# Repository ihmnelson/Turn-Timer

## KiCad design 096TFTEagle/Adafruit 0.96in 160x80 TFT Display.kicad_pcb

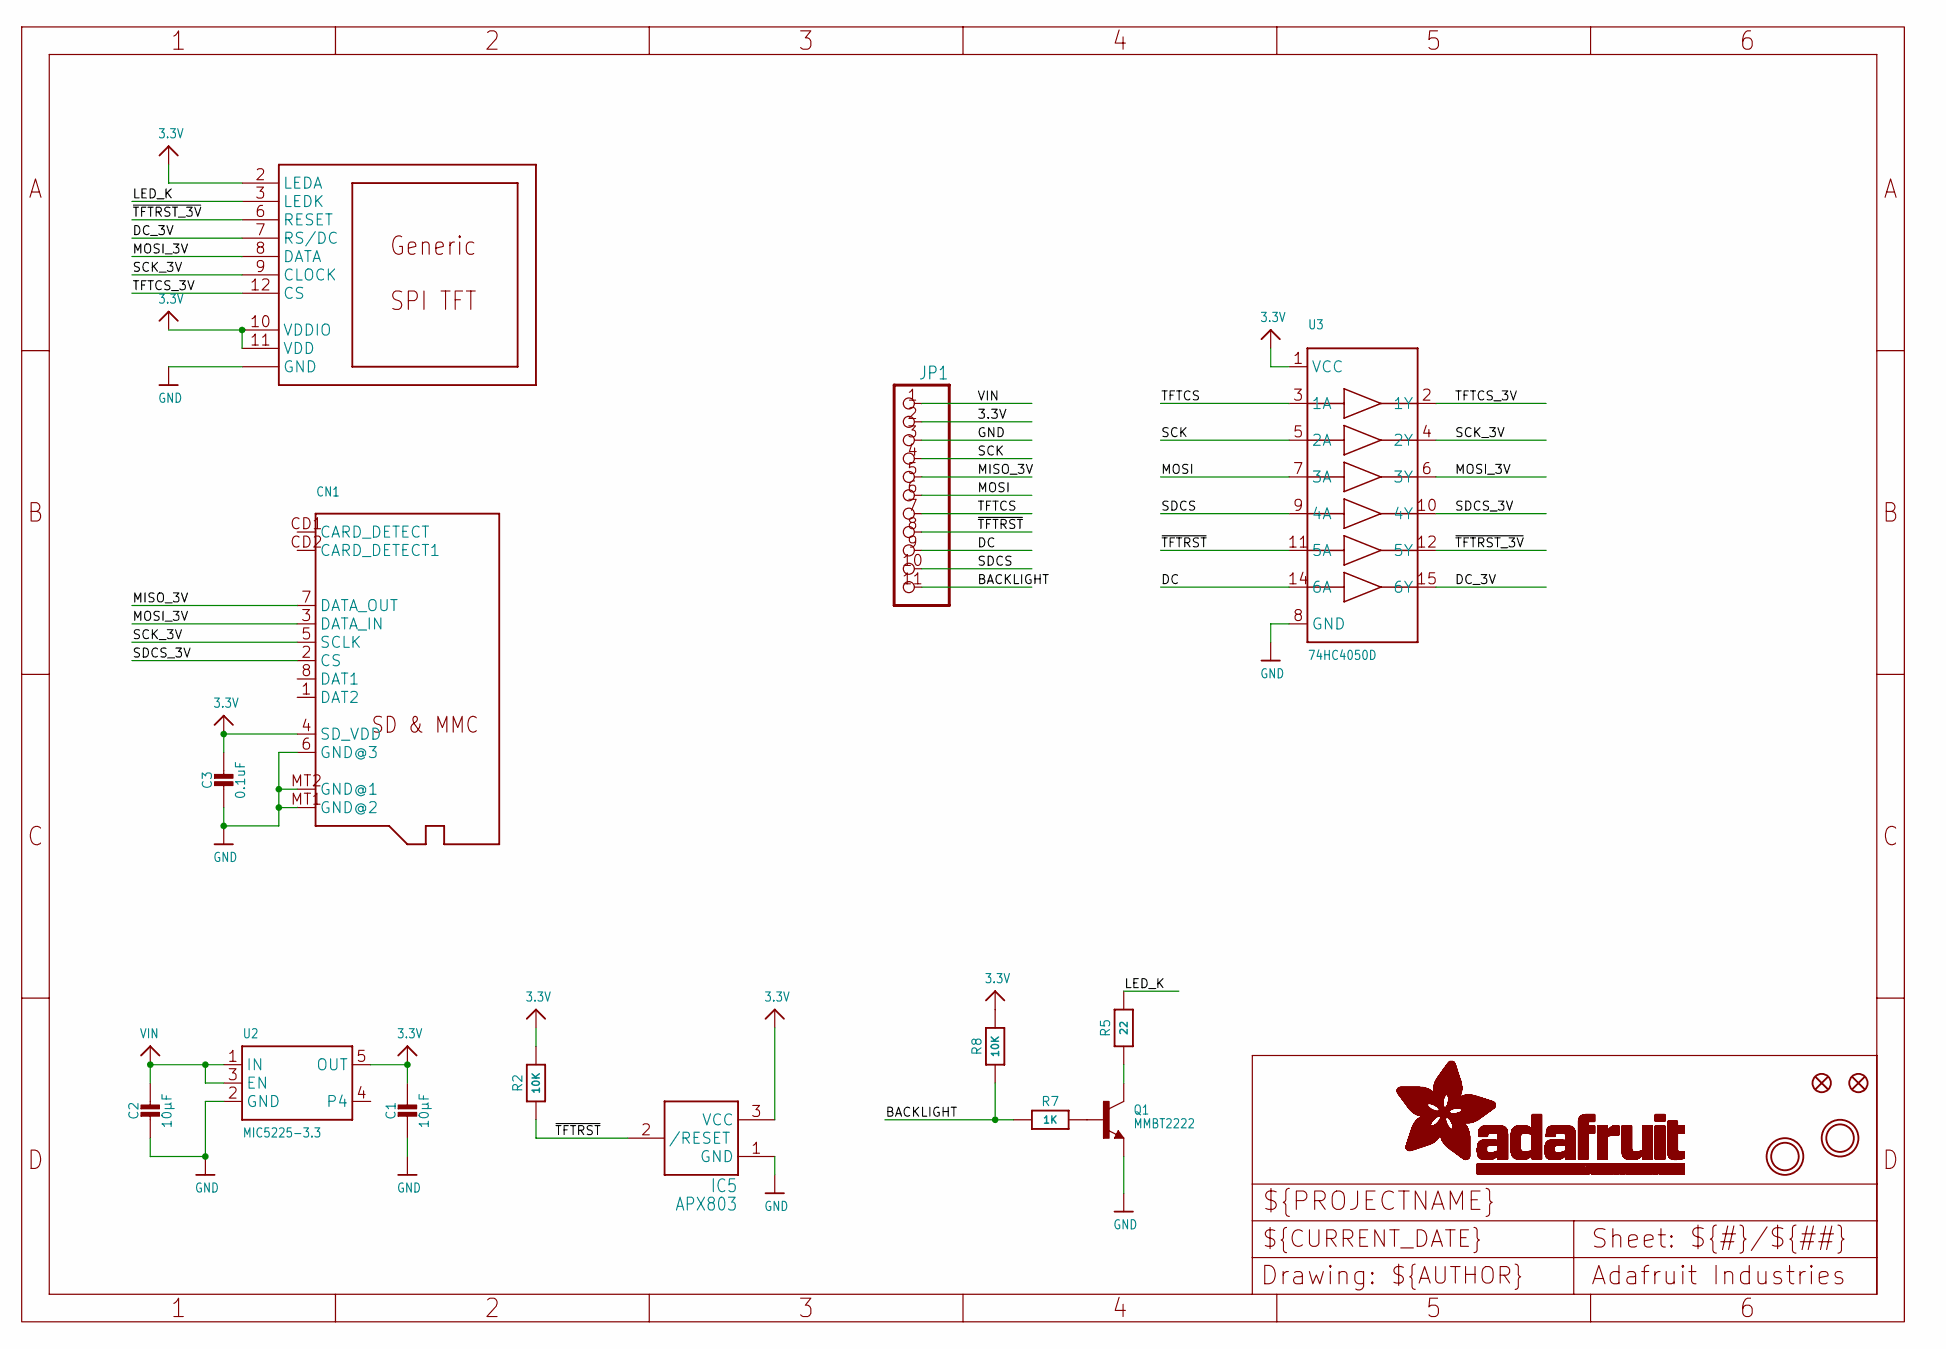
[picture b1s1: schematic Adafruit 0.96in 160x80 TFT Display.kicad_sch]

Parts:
C1, C2: 10µF; 0805-NO
C3: 0.1uF; 0805-NO
CN1: MICROSD
FID1, FID2: FIDUCIAL_1MM
IC5: APX803; SOT23
JP1: HEADER-1X11; 1X11_ROUND
Q1: MMBT2222; SOT23-WIDE
R2, R8: 10K; 0603-NO
R5: 22; 0603-NO
R7: 1K; 0603-NO
U2: MIC5225-3.3; SOT23-5
U3: 74HC4050D; SOIC16
U$2: DISP_LCD_0.9IN_160X80; TFT_0.96IN_160X80
U$9, U$10: MOUNTINGHOLE2.5; MOUNTINGHOLE_2.5_PLATED

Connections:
3.3V: C1.1, C3.1, CN1.4 (SD_VDD), IC5.3 (VCC), JP1.2, R2.2, R8.2, U2.5 (OUT), U3.1 (VCC), U$2.2 (LEDA), U$2.10 (VDDIO), U$2.11 (VDD)
BACKLIGHT: JP1.11, R7.1, R8.1
DC: JP1.9, U3.14 (6A)
DC_3V: U3.15 (6Y), U$2.7 (RS/DC)
GND: C1.2, C2.2, C3.2, CN1.6 (GND@3), CN1.MT1 (GND@2), CN1.MT2 (GND@1), IC5.1 (GND), JP1.3, Q1.2 (E), U2.2 (GND), U3.8 (GND), U$2.1 (GND), U$2.5 (GND), U$2.13 (GND)
LED_K: R5.2, U$2.3 (LEDK)
MISO_3V: CN1.7 (DATA_OUT), JP1.5
MOSI: JP1.6, U3.7 (3A)
MOSI_3V: CN1.3 (DATA_IN), U3.6 (3Y), U$2.8 (DATA)
unnamed: Q1.1 (B), R7.2
unnamed: Q1.3 (C), R5.1
SCK: JP1.4, U3.5 (2A)
SCK_3V: CN1.5 (SCLK), U3.4 (2Y), U$2.9 (CLOCK)
SDCS: JP1.10, U3.9 (4A)
SDCS_3V: CN1.2 (CS), U3.10 (4Y)
TFTCS: JP1.7, U3.3 (1A)
TFTCS_3V: U3.2 (1Y), U$2.12 (CS)
VIN: C2.1, JP1.1, U2.1 (IN), U2.3 (EN)
~TFTRST_3V: U3.12 (5Y), U$2.6 (RESET)
~TFTRST: IC5.2 (/RESET), JP1.8, R2.1, U3.11 (5A)

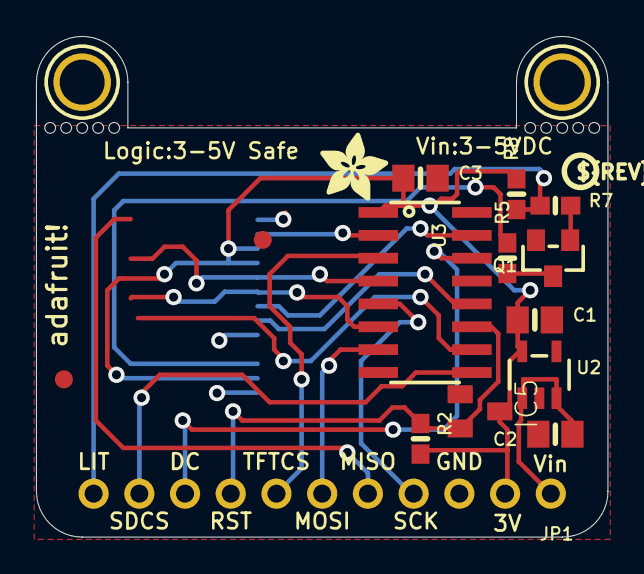
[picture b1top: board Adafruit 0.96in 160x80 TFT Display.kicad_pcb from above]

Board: 2 copper layers, 31.8 x 27.8 mm, 29 parts (1 on the bottom side), 18 nets.

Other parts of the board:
U$4: MICROSD; ADAFRUIT_3.5MM
U$6: PCBFEAT-REV-040
UNK_HOLE_0: dummyfp0
UNK_HOLE_1: dummyfp1
UNK_HOLE_2: dummyfp2
UNK_HOLE_3: dummyfp3
UNK_HOLE_4: dummyfp4
UNK_HOLE_5: dummyfp5
UNK_HOLE_6: dummyfp6
UNK_HOLE_7: dummyfp7
UNK_HOLE_8: dummyfp8
UNK_HOLE_9: dummyfp9

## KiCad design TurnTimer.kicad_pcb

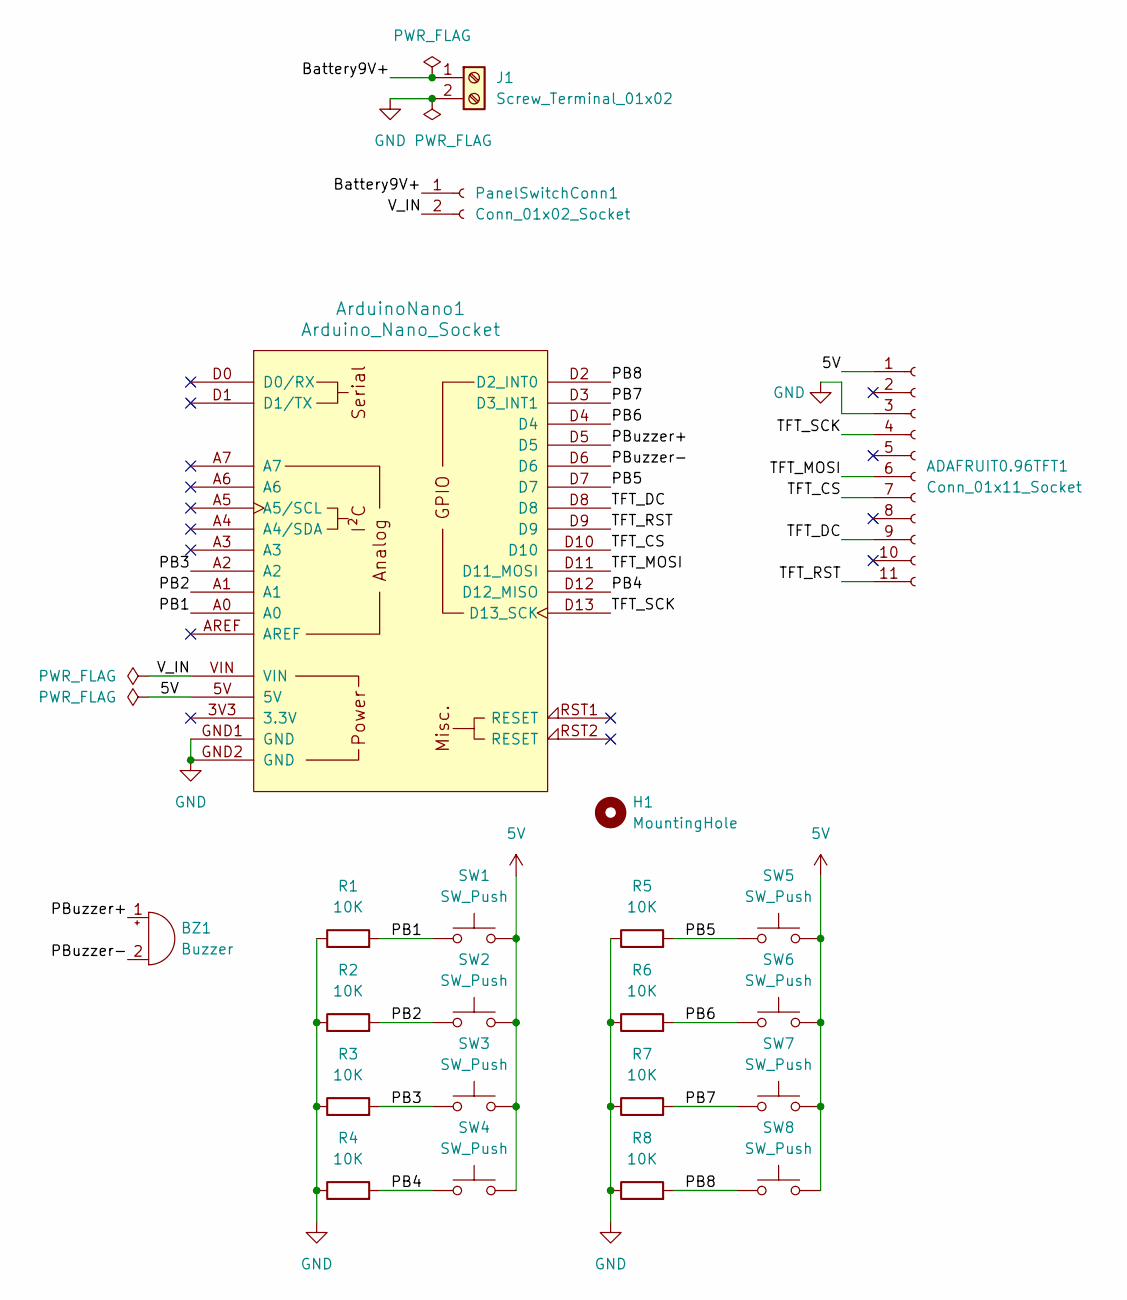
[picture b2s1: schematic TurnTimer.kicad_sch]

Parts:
ADAFRUIT0.96TFT1: Conn_01x11_Socket; PinHeader_1x11_P2.54mm_Vertical
ArduinoNano1: Arduino_Nano_Socket
BZ1: Buzzer; Buzzer_TDK_PS1240P02BT_D12.2mm_H6.5mm
H1: MountingHole; MountingHole_3.2mm_M3
J1: Screw_Terminal_01x02; TerminalBlock_CUI_TB007-508-02_1x02_P5.08mm_Horizontal
PanelSwitchConn1: Conn_01x02_Socket; PinHeader_1x02_P2.54mm_Vertical
R1, R2, R3, R4, R5, R6, R7, R8: 10K; R_Axial_DIN0207_L6.3mm_D2.5mm_P10.16mm_Horizontal
SW1, SW2, SW3, SW4, SW5, SW6, SW7, SW8: SW_Push; SW_Cherry_MX_1.00u_PCB

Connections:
5V: ADAFRUIT0.96TFT1.1, ArduinoNano1.5V, SW1.2, SW2.2, SW3.2, SW4.2, SW5.2, SW6.2, SW7.2, SW8.2
/Battery9V+: J1.1, PanelSwitchConn1.1
/PB1: ArduinoNano1.A0, R1.2, SW1.1
/PB2: ArduinoNano1.A1, R2.2, SW2.1
/PB3: ArduinoNano1.A2, R3.2, SW3.1
/PB4: ArduinoNano1.D12 (D12_MISO), R4.2, SW4.1
/PB5: ArduinoNano1.D7, R5.2, SW5.1
/PB6: ArduinoNano1.D4, R6.2, SW6.1
/PB7: ArduinoNano1.D3 (D3_INT1), R7.2, SW7.1
/PB8: ArduinoNano1.D2 (D2_INT0), R8.2, SW8.1
/PBuzzer+: ArduinoNano1.D5, BZ1.1 (+)
/PBuzzer-: ArduinoNano1.D6, BZ1.2 (-)
/TFT_CS: ADAFRUIT0.96TFT1.7, ArduinoNano1.D10
/TFT_DC: ADAFRUIT0.96TFT1.9, ArduinoNano1.D8
/TFT_MOSI: ADAFRUIT0.96TFT1.6, ArduinoNano1.D11 (D11_MOSI)
/TFT_RST: ADAFRUIT0.96TFT1.11, ArduinoNano1.D9
/TFT_SCK: ADAFRUIT0.96TFT1.4, ArduinoNano1.D13 (D13_SCK)
/V_IN: ArduinoNano1.VIN, PanelSwitchConn1.2
GND: ADAFRUIT0.96TFT1.3, ArduinoNano1.GND1 (GND), ArduinoNano1.GND2 (GND), J1.2, R1.1, R2.1, R3.1, R4.1, R5.1, R6.1, R7.1, R8.1

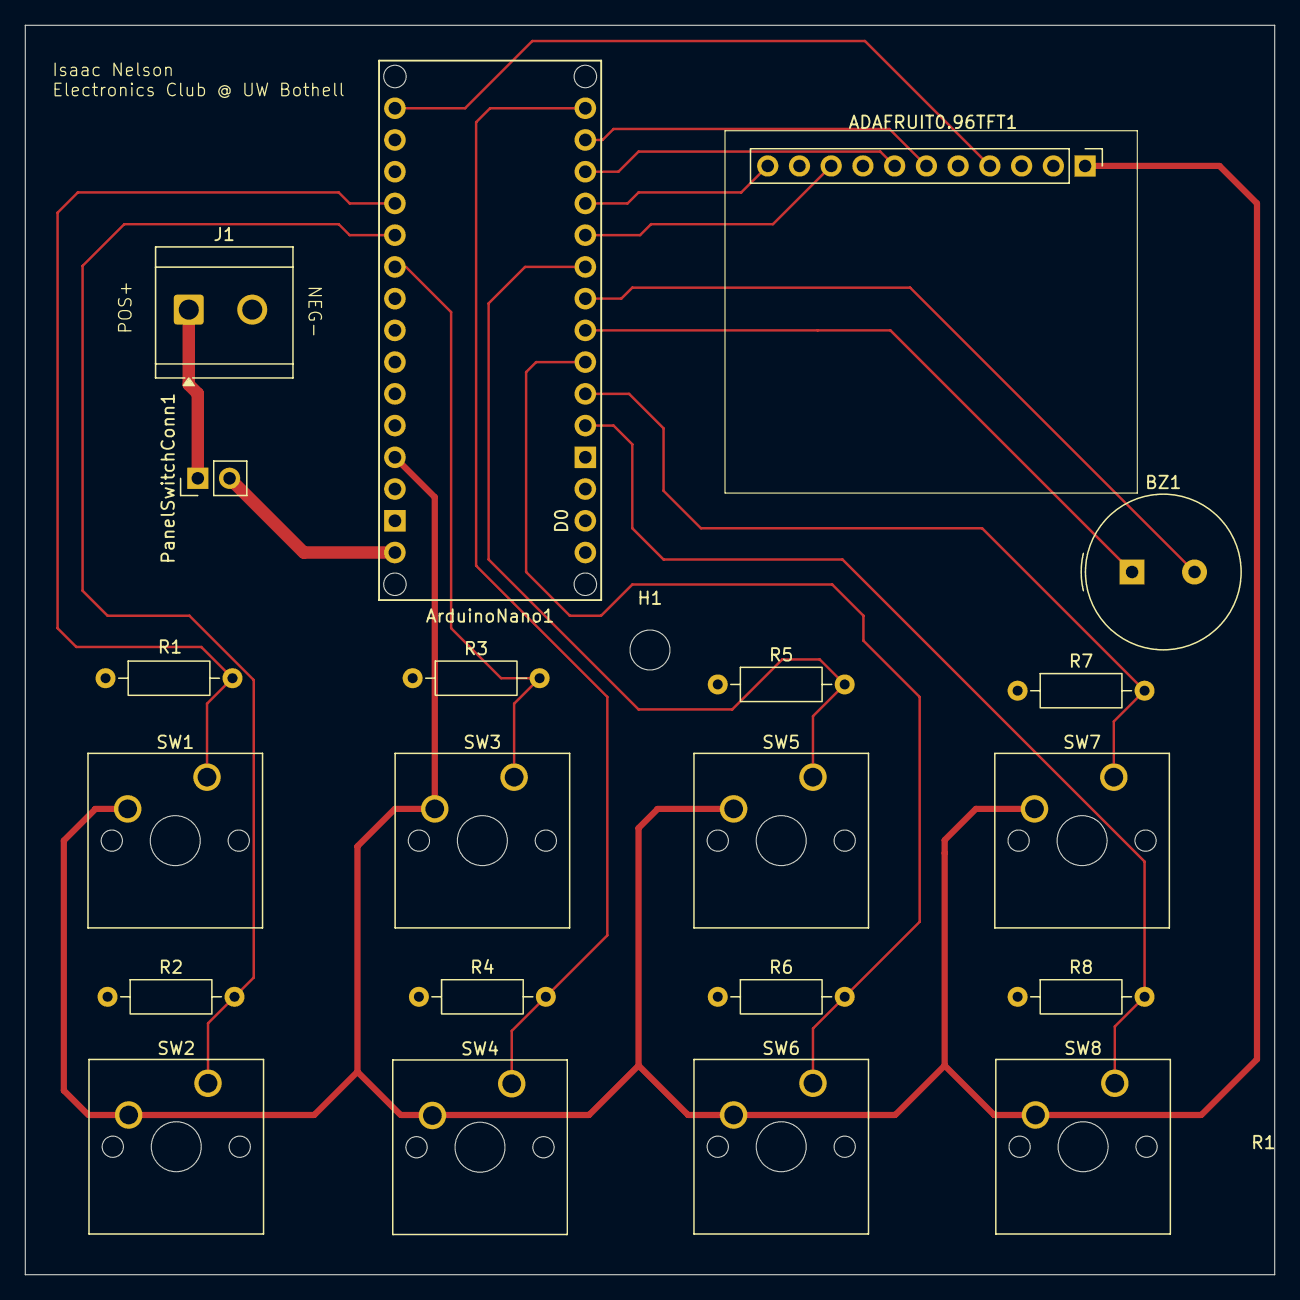
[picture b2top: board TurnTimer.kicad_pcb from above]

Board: 2 copper layers, 100.0 x 100.0 mm, 22 parts (0 on the bottom side), 19 nets.

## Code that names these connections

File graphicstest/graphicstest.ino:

#include <Adafruit_GFX.h>
#include <Adafruit_ST7735.h>
#include <SPI.h>

#define TFT_CS  10
#define TFT_DC   8
#define TFT_RST -1
#define LED_PIN 13

#define NUM_BUTTONS 8
const int BUTTON_PINS[NUM_BUTTONS] = {7, 6, 5, 4, 3, 2, A0, A1};

Adafruit_ST7735 tft = Adafruit_ST7735(TFT_CS, TFT_DC, TFT_RST);

// ---- Settings ----
int maxTime = 480;
int playerTime[6];
int activePlayer = -1;
bool running = false;

// ---- Button state ----
bool buttonState[NUM_BUTTONS];
bool lastButtonState[NUM_BUTTONS];
unsigned long lastTick = 0;

// ---- Hourglass ----
int hourglassFrame = 0;
unsigned long lastHourglassUpdate = 0;

// ---- Helpers ----
bool justPressed(int i) {
  return buttonState[i] && !lastButtonState[i];
}

void readButtons() {
  for (int i = 0; i < NUM_BUTTONS; i++) {
    lastButtonState[i] = buttonState[i];
    buttonState[i] = digitalRead(BUTTON_PINS[i]) == HIGH;
  }
}

void formatTime(int seconds, char* buf) {
  sprintf(buf, "%d:%02d", seconds / 60, seconds % 60);
}

// ---- Timeout Flash ----
void flashTimeout() {
  // Stop clock and flash screen red/black 5 times
  running = false;
  for (int f = 0; f < 5; f++) {
    tft.fillScreen(ST77XX_RED);
    digitalWrite(LED_PIN, HIGH);
    delay(200);
    tft.fillScreen(ST77XX_BLACK);
    digitalWrite(LED_PIN, LOW);
    delay(200);
  }
  // Advance to next player but don't start their clock
  int next = (activePlayer + 1) % 6;
  activePlayer = next;
  running = false;
  drawScreen();
}

// ---- Hourglass ----
// Draws a large hourglass in the right half of the screen
// x,y = top left corner, w/h = bounding box
void drawHourglass(int x, int y, int w, int h, float fraction, uint16_t color) {
  // fraction = 1.0 full, 0.0 empty
  int cx = x + w / 2;
  int midY = y + h / 2;

  // Clear area
  tft.fillRect(x, y, w, h, ST77XX_BLACK);

  // Top triangle outline
  tft.drawTriangle(x, y, x + w, y, cx, midY, color);
  // Bottom triangle outline
  tft.drawTriangle(x, y + h, x + w, y + h, cx, midY, color);

  // Fill top triangle (sand draining) - fill from bottom of top triangle up
  if (fraction > 0) {
    int sandH = (int)((midY - y) * fraction);
    // Fill top sand - shrinking triangle from top
    for (int row = 0; row < sandH; row++) {
      float t = (float)row / (midY - y);
      int rowW = (int)(w * t);
      int rowX = cx - rowW / 2;
      tft.drawFastHLine(rowX, y + row, rowW, color);
    }
  }

  // Fill bottom triangle (sand collecting) - fill from bottom up
  if (fraction < 1.0) {
    int sandH = (int)((midY - y) * (1.0 - fraction));
    for (int row = 0; row < sandH; row++) {
      float t = (float)row / (midY - y);
      int rowW = (int)(w * t);
      int rowX = cx - rowW / 2;
      tft.drawFastHLine(rowX, y + h - row, rowW, color);
    }
  }

  // Neck dot
  tft.fillCircle(cx, midY, 2, color);
}

void updateHourglass() {
  if (activePlayer < 0) return;

  float fraction = (float)playerTime[activePlayer] / maxTime;
  fraction = constrain(fraction, 0.0, 1.0);

  uint16_t col = running ? ST77XX_CYAN : ST77XX_YELLOW;
  drawHourglass(88, 14, 68, 52, fraction, col);

  // Big time display centered below hourglass
  char buf[10];
  formatTime(playerTime[activePlayer], buf);
  tft.setTextSize(2);
  tft.setTextColor(col);
  // Clear old time
  tft.fillRect(88, 68, 72, 12, ST77XX_BLACK);
  tft.setCursor(92, 68);
  tft.print(buf);
  tft.setTextSize(1);
}

// ---- Display ----
void drawScreen() {
  tft.fillScreen(ST77XX_BLACK);

  // Top bar
  tft.setTextSize(1);
  tft.setTextColor(ST77XX_CYAN);
  tft.setCursor(2, 2);
  tft.print("Max:");
  char buf[10];
  formatTime(maxTime, buf);
  tft.print(buf);
  tft.setTextColor(ST77XX_WHITE);
  tft.setCursor(55, 2);
  tft.print("B0:rst B1:+30s");

  tft.drawFastHLine(0, 12, 160, ST77XX_WHITE);

  // Vertical divider between player list and hourglass
  tft.drawFastVLine(87, 12, 68, ST77XX_WHITE);

  // Player rows on left half
  for (int i = 0; i < 6; i++) {
    drawPlayer(i);
  }

  // Hourglass on right
  if (activePlayer >= 0) {
    updateHourglass();
  }
}

void drawPlayer(int i) {
  int y = 15 + (i * 10);

  uint16_t bg = ST77XX_BLACK;
  if (i == activePlayer) {
    bg = running ? ST77XX_GREEN : ST77XX_YELLOW;
  }
  tft.fillRect(0, y, 86, 9, bg);

  uint16_t fg = (i == activePlayer) ? ST77XX_BLACK : ST77XX_WHITE;
  if (playerTime[i] <= 0) fg = ST77XX_RED;

  tft.setTextColor(fg);
  tft.setTextSize(1);

  tft.setCursor(2, y + 1);
  tft.print("P");
  tft.print(i + 1);

  char buf[10];
  formatTime(playerTime[i], buf);
  tft.setCursor(22, y + 1);
  tft.print(buf);

  // Small status indicator
  if (i == activePlayer) {
    tft.setCursor(58, y + 1);
    tft.print(running ? "RUN" : "PAU");
  }
}

// ---- Reset ----
void resetAll() {
  for (int i = 0; i < 6; i++) {
    playerTime[i] = maxTime;
  }
  activePlayer = -1;
  running = false;
  digitalWrite(LED_PIN, LOW);
  drawScreen();
}

// ---- Main ----
void setup() {
  pinMode(LED_PIN, OUTPUT);
  for (int i = 0; i < NUM_BUTTONS; i++) {
    pinMode(BUTTON_PINS[i], INPUT);
  }

  tft.initR(INITR_MINI160x80_PLUGIN);
  tft.setRotation(1);

  resetAll();
}

void loop() {
  readButtons();

  // Button 0: reset
  if (justPressed(0)) {
    resetAll();
  }

  // Button 1: +30s to max, loop at 10 min
  if (justPressed(1)) {
    maxTime += 30;
    if (maxTime > 600) maxTime = 30;
    resetAll();
  }

  // Buttons 2-7: players
  for (int i = 0; i < 6; i++) {
    if (justPressed(i + 2)) {
      if (i == activePlayer) {
        // Toggle pause/run your own timer
        running = !running;
        if (running) lastTick = millis();
        drawPlayer(i);
        updateHourglass();
      } else {
        // Switch to this player, don't auto-start
        int old = activePlayer;
        activePlayer = i;
        running = false;
        if (old >= 0) drawPlayer(old);
        drawPlayer(i);
        updateHourglass();
      }
    }
  }

  // Tick timer
  if (running && activePlayer >= 0) {
    unsigned long now = millis();
    if (now - lastTick >= 1000) {
      lastTick = now;
      playerTime[activePlayer]--;

      if (playerTime[activePlayer] <= 0) {
        playerTime[activePlayer] = 0;
        drawPlayer(activePlayer);
        updateHourglass();
        flashTimeout();
      } else {
        drawPlayer(activePlayer);
        updateHourglass();
      }
    }
  }

  // Animate hourglass while running
  if (running && activePlayer >= 0) {
    unsigned long now = millis();
    if (now - lastHourglassUpdate >= 2000) {
      lastHourglassUpdate = now;
      updateHourglass();
    }
  }

  delay(20);
}

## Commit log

2026-05-19 first commit with existing files
2026-05-19 second commit?
2026-05-21 absorbed 096 into one repo
2026-05-21 removed sub .history from 096
2026-05-21 removed unecessary files
2026-05-21 not even sure just new gitignore
2026-05-21 cleaning up repo
2026-05-21 help
2026-05-21 updated 3d models on kicad reneder
